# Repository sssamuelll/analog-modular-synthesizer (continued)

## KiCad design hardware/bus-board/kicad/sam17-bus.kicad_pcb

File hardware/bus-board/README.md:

# Bus board — distribución de ±12 V

Reparte los rieles del [módulo 1](../01-power-supply/) a los módulos. Sustituye
al daisy-chain con cables jumper de la tesis, que era la fuente de ruido y de
desafinación que la propia tesis reportó.

Se construyen **dos segmentos idénticos** de 320 × 60 mm. Cada uno lleva 6
slots y se alimenta con su propio par de cables desde el punto de estrella.

## Qué decide esta placa

No es un problema de corriente, es de **afinación**. A 1 V/octava, **1 mV de
diferencia de masa entre dos módulos son 1.2 cents** de error de tono. El
objetivo es ≤ 2 cents entre los cuatro módulos de la cadena de tono, y de ahí
sale todo lo demás.

| | |
|---|---|
| Presupuesto de masa medido | **1.21 cents** ([`ground_budget.py`](ground_budget.py)) |
| Masa | **plano sólido en B.Cu** — con pista de 5 mm serían +7.1 cents |
| Vías | **0** — una vía de señal le abre una ranura al plano |
| De dónde venimos | daisy-chain de la tesis: 6.3–30 cents |

El resultado que no esperaba: **el plano aporta solo 0.20 cents; el resto se lo
come el cable de bajada**. Y dentro del cable manda el contacto crimpado, no el
cobre. Detalle en [`notes/design-notes.md`](notes/design-notes.md).

## Por slot

- **Peine Eurorack 2×8 sin llave** — Doepfer prohíbe expresamente los headers
  con caja y código en un bus board. La franja roja va al par **−12 V**,
  serigrafiado. El +5 V, CV y Gate quedan **NC a propósito** (§9 de las notas).
- **Peine SAM17 KK-254 de 4 pines, con llave** — el mismo `J2` del módulo 1.
- **Dos PTC de 0.25 A**, uno por riel. **Nunca en masa**: ahí serían 94 cents.
- **Dos LED con 4k7** en paralelo con cada PTC. Apagados en marcha, encendidos
  cuando ese fusible dispara. Señalan el conector y el riel culpables.

## Estructura

```
bus-board/
├── ground_budget.py     El presupuesto de masa, ejecutable y con aserciones
├── bom.csv
├── kicad/
│   ├── symlib.py            Extrae simbolos de las librerias de KiCad
│   ├── build_schematic.py   Genera sam17-bus.kicad_sch (sin MCP: kicad-cli)
│   ├── check_netlist.py     Netlist contra el diseño declarado a mano
│   ├── check_bom.py         Cruce esquemático <-> bom.csv
│   ├── build_pcb.py         Genera sam17-bus.kicad_pcb (pcbnew directo)
│   └── sam17.pretty/        Huella propia del PTC (admite dos encapsulados)
├── schematics/ pcb/ fab/
└── notes/design-notes.md
```

## Estado

- [x] Presupuesto de masa cerrado y ejecutable — **1.21 cents** de 2
- [x] Esquemático — 49 componentes, **ERC 0 infracciones**
- [x] Netlist verificado contra el diseño: 27 redes, 160 pines, uno a uno
- [x] PCB — 320 × 60 mm, 2 capas, **DRC 0 infracciones, 0 sin conectar, 0 vías**
- [x] Masa en B.Cu verificada por id de capa (el nombre de capa engaña)
- [x] Gerbers y taladros en [`fab/`](fab/)
- [ ] **Antes de fabricar**: verificar con polímetro el orden de filas del peine
      Eurorack contra un cable Doepfer real. Está confirmado que la franja roja
      es −12 V; el orden del bloque central sale de fuentes secundarias
      ([§12.1](notes/design-notes.md))
- [ ] Medir la resistencia de contacto real del crimpado — es el término que más
      pesa del presupuesto y el valor usado es de manual
- [ ] Medir la diferencia de masa entre slots con los módulos montados

## Reglas de montaje que no se pueden saltar

1. **La cadena de tono (MIDI/CV + VCO1..3) va entera en el mismo segmento.**
   Repartida entre los dos, el desequilibrio entre sus cables de alimentación se
   les suma completo.
2. **Los dos hilos de masa del cable SAM17 se crimpan siempre.** Con uno solo el
   presupuesto se sale de los 2 cents.
3. **Cables de bajada ≤ 150 mm.** A 500 mm se añade ~1 cent.
4. **Separadores de nylon, no metálicos.** El puente chasis-masa es uno y está
   en el módulo 1 ([§13](../01-power-supply/notes/design-notes.md)).
5. **Cada segmento se alimenta desde el punto de estrella**, con pares de
   2.5 mm² de longitud parecida. No encadenar un segmento del otro.
6. **Franja roja del cable al par serigrafiado −12 V.** Siempre.

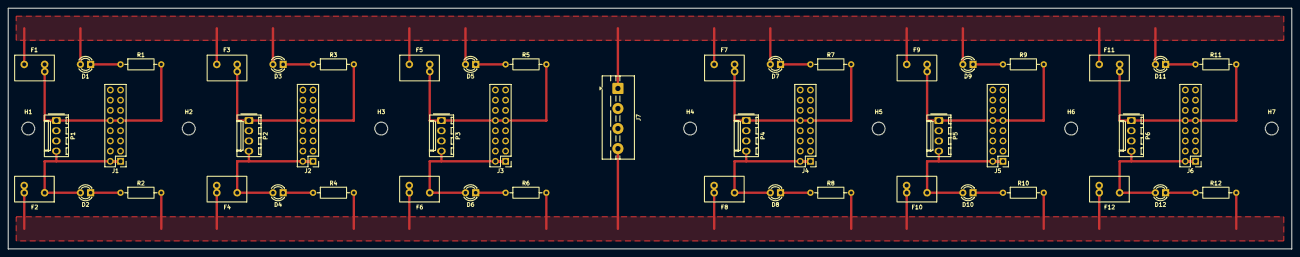
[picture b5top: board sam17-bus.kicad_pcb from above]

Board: 2 copper layers, 320.0 x 60.0 mm, 56 parts (0 on the bottom side), 27 nets.

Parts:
D1, D2, D3, D4, D5, D6, D7, D8, D9, D10, D11, D12: LED_D3.0mm
F1, F2, F3, F4, F5, F6, F7, F8, F9, F10, F11, F12: PTC_Radial_P5.08mm_Dual
H1, H2, H3, H4, H5, H6, H7: MountingHole_3.2mm_M3
J1, J2, J3, J4, J5, J6: PinHeader_2x08_P2.54mm_Vertical
J7: TerminalBlock_MaiXu_MX126-5.0-04P_1x04_P5.00mm
P1, P2, P3, P4, P5, P6: Molex_KK-254_AE-6410-04A_1x04_P2.54mm_Vertical
R1, R2, R3, R4, R5, R6, R7, R8, R9, R10, R11, R12: R_Axial_DIN0207_L6.3mm_D2.5mm_P10.16mm_Horizontal

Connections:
+12S1: F1.2, J1.9, J1.10, P1.1, R1.2
+12S2: F3.2, J2.9, J2.10, P2.1, R3.2
+12S3: F5.2, J3.9, J3.10, P3.1, R5.2
+12S4: F7.2, J4.9, J4.10, P4.1, R7.2
+12S5: F9.2, J5.9, J5.10, P5.1, R9.2
+12S6: F11.2, J6.9, J6.10, P6.1, R11.2
+12V: D1.2, D3.2, D5.2, D7.2, D9.2, D11.2, F1.1, F3.1, F5.1, F7.1, F9.1, F11.1, J7.1
-12S1: D2.2, F2.1, J1.1, J1.2, P1.4
-12S2: D4.2, F4.1, J2.1, J2.2, P2.4
-12S3: D6.2, F6.1, J3.1, J3.2, P3.4
-12S4: D8.2, F8.1, J4.1, J4.2, P4.4
-12S5: D10.2, F10.1, J5.1, J5.2, P5.4
-12S6: D12.2, F12.1, J6.1, J6.2, P6.4
-12V: F2.2, F4.2, F6.2, F8.2, F10.2, F12.2, J7.4, R2.2, R4.2, R6.2, R8.2, R10.2, R12.2
GND: J1.3, J1.4, J1.5, J1.6, J1.7, J1.8, J2.3, J2.4, J2.5, J2.6, J2.7, J2.8, J3.3, J3.4, J3.5, J3.6, J3.7, J3.8, J4.3, J4.4, J4.5, J4.6, J4.7, J4.8, J5.3, J5.4, J5.5, J5.6, J5.7, J5.8, J6.3, J6.4, J6.5, J6.6, J6.7, J6.8, J7.2, J7.3, P1.2, P1.3, P2.2, P2.3, P3.2, P3.3, P4.2, P4.3, P5.2, P5.3, P6.2, P6.3
unnamed: D1.1, R1.1
unnamed: D2.1, R2.1
unnamed: D3.1, R3.1
unnamed: D4.1, R4.1
unnamed: D5.1, R5.1
unnamed: D6.1, R6.1
unnamed: D7.1, R7.1
unnamed: D8.1, R8.1
unnamed: D9.1, R9.1
unnamed: D10.1, R10.1
unnamed: D11.1, R11.1
unnamed: D12.1, R12.1

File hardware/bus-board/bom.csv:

refs,value,footprint,quantity,supplier,notes
J1 J2 J3 J4 J5 J6,"Tira de pines 2x8 2.54 mm RECTA, SIN caja",Connector_PinHeader_2.54mm:PinHeader_2x08_P2.54mm_Vertical,6,Reichelt,"Peine Eurorack. SIN caja y SIN llave, y esto NO es un ahorro: Doepfer lo prohibe expresamente — 'it's not allowed to use bus boards with polarized pin headers (boxed pin headers with code gap). These force the user to connect the bus cable in a certain direction which may be the wrong one'. La orientacion la da la franja roja del cable = -12 V = par de abajo, serigrafiado en la placa. Si compras version con caja, la caja decide por ti y puede decidir mal"
P1 P2 P3 P4 P5 P6,"Molex KK-254 4 pines vertical (macho de PCB)",Connector_Molex:Molex_KK-254_AE-6410-04A_1x04_P2.54mm_Vertical,6,Mouser,"Peine SAM17. La MISMA pieza que J2 del modulo 1, para que el cable de bajada sea macho-hembra del mismo sistema. Aqui la llave SI se quiere: es un conector propietario, no hay estandar ajeno que respetar, y la llave impide invertirlo"
J7,"Bornero de tornillo 4 pos, paso 5 mm, >=2.5 mm2",TerminalBlock:TerminalBlock_MaiXu_MX126-5.0-04P_1x04_P5.00mm,1,Reichelt,"Entrada desde el punto de estrella del modulo 1: +12 / GND / GND / -12. Los DOS tornillos de masa se usan: dividen por dos la resistencia de contacto del feed. Que admita 2.5 mm2 no es capricho — con 1.5 mm2 el desequilibrio entre los dos segmentos se come 1 cent del presupuesto (ground_budget.py)"
F1 F2 F3 F4 F5 F6 F7 F8 F9 F10 F11 F12,"PTC reajustable 0.25 A hold / 0.50 A trip, >=30 V",sam17:PTC_Radial_P5.08mm_Dual,12,Mouser,"Bel Fuse 0ZRE0025FF1E (Ihold 0.25 A, Itrip 0.56 A, 240 V, R 1.3 ohm typ). Alternativa Bourns MF-R025 (Ihold 0.25 A, Itrip 0.50 A, 60 V, Rmin 1.00 / R1max 1.95 ohm) — la huella admite las DOS porque el pad 2 esta duplicado (patillas en linea o escalonadas). Se puebla UNO de los dos taladros. **Van en +12 V y en -12 V, JAMAS en masa**: 1.3 ohm en el retorno son 94 cents de desafinacion"
D1 D2 D3 D4 D5 D6 D7 D8 D9 D10 D11 D12,"LED 3 mm rojo difuso, alta eficiencia",LED_THT:LED_D3.0mm,12,Reichelt,"Indicador de PTC disparado, en paralelo con su fusible. Apagado en marcha (caen ~0.1 V sobre el PTC intacto) y encendido a ~2 mA cuando el PTC dispara y quedan los 12 V. Que sea de alta eficiencia importa: a 2 mA un LED antiguo no se ve. Dos por slot, uno por riel, porque el riel que falla es la mitad del diagnostico"
R1 R2 R3 R4 R5 R6 R7 R8 R9 R10 R11 R12,"4k7 1/4 W 5%",Resistor_THT:R_Axial_DIN0207_L6.3mm_D2.5mm_P10.16mm_Horizontal,12,Reichelt,"Limitadora del LED indicador. 4k7 da ~2.1 mA con 12 V sobre el PTC disparado. No bajar mucho: la rama roba corriente al PTC y este necesita seguir calentandose solo para quedarse disparado (a 12 V pide ~40 mA, asi que 2 mA no le molestan)"
H1 H2 H3 H4 H5 H6 H7,"Separador de NYLON M3 + tornillo de nylon",MountingHole:MountingHole_3.2mm_M3,7,Reichelt,"NYLON, no metal. Siete esparragos metalicos unirian el plano de masa al chasis en siete puntos y meterian corriente de chasis por el plano — justo lo que el presupuesto de masa da por supuesto que no pasa. El puente chasis-GND es UNO y esta en el modulo 1 (§13)"
—,"Cable de bajada SAM17: 4 hilos 24 AWG, <=150 mm",n/a,6,Reichelt,"Macho-hembra KK-254 de 4 vias. **Los dos hilos de masa se crimpan siempre**: con uno solo el presupuesto se dobla y se sale de los 2 cents. Y <=150 mm: a 500 mm se anaden ~1 cent. Engordar a 20 AWG casi no mejora — a esta escala mandan los contactos crimpados, no el cobre"
—,"Cable de bajada Eurorack: cinta 16 vias, <=150 mm",n/a,6,Thomann/Schneidersladen,"Cinta IDC estandar de 16 vias con franja roja. La franja va SIEMPRE al par de abajo, el serigrafiado -12V. Sus 6 conductores de masa en paralelo compensan que sea 28 AWG: sale a 9.1 mohm, mejor que los 16.8 del cable SAM17 de 24 AWG con solo dos"
—,"Alimentacion desde el modulo 1: 2.5 mm2, par por segmento",n/a,2,Reichelt,"Un par +12/GND/-12 por SEGMENTO, los dos saliendo del MISMO punto de estrella y lo mas iguales de largo que se pueda. Encadenar un segmento del otro seria mas comodo y mete la caida del primero en el segundo"

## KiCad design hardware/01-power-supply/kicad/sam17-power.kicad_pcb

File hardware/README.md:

# Hardware

Esquemáticos, PCBs y BOMs para los 7 módulos del SAM17.

| Módulo | Carpeta | Documentación |
|--------|---------|---------------|
| 1 — Alimentación | [`01-power-supply/`](01-power-supply) | [`docs/modules/01-power-supply.md`](../docs/modules/01-power-supply.md) |
| 2 — MIDI/CV | [`02-midi-cv/`](02-midi-cv) | [`docs/modules/02-midi-cv.md`](../docs/modules/02-midi-cv.md) |
| 3 — VCO | [`03-vco/`](03-vco) | [`docs/modules/03-vco.md`](../docs/modules/03-vco.md) |
| 4 — Mixer | [`04-mixer/`](04-mixer) | [`docs/modules/04-mixer.md`](../docs/modules/04-mixer.md) |
| 5 — VCF | [`05-vcf/`](05-vcf) | [`docs/modules/05-vcf.md`](../docs/modules/05-vcf.md) |
| 6 — ADSR | [`06-adsr/`](06-adsr) | [`docs/modules/06-adsr.md`](../docs/modules/06-adsr.md) |
| 7 — VCA | [`07-vca/`](07-vca) | [`docs/modules/07-vca.md`](../docs/modules/07-vca.md) |

Y una placa que no es un módulo de la tesis pero sin la cual los módulos no
afinan entre sí:

| Placa | Carpeta | Qué decide |
|---|---|---|
| Bus board | [`bus-board/`](bus-board) | Reparte ±12 V a todos. **1 mV de diferencia de masa entre dos módulos = 1.2 cents de desafinación**; el presupuesto está en [`bus-board/ground_budget.py`](bus-board/ground_budget.py) y sale a 1.21 de 2 |

## Estructura por módulo

Cada subdirectorio sigue la misma convención:

```
NN-<módulo>/
├── README.md            Resumen, especificaciones y mejoras
├── kicad/               Proyecto KiCad (.kicad_pro, .kicad_sch, .kicad_pcb)
├── schematics/          Esquemáticos exportados a PDF
├── pcb/                 Renderizados PCB (PNG/SVG/3D)
├── bom.csv              Lista de materiales
└── notes/               Notas de diseño, mediciones, calibración
```

## Convenciones eléctricas

Ver [`docs/architecture.md`](../docs/architecture.md) para el detalle del bus
de alimentación, niveles de señal y estándar 1 V/octava compartido por
todos los módulos.

## Estado actual

Este es el esqueleto inicial: los proyectos KiCad, esquemáticos y PCBs
todavía no están versionados. Las BOM contienen una **versión preliminar**
extraída de la tesis (Tabla 8 y 9 de la evaluación económica). Si vas a
empezar a capturar el esquemático de un módulo, abre primero un *issue*
para evitar trabajo duplicado.

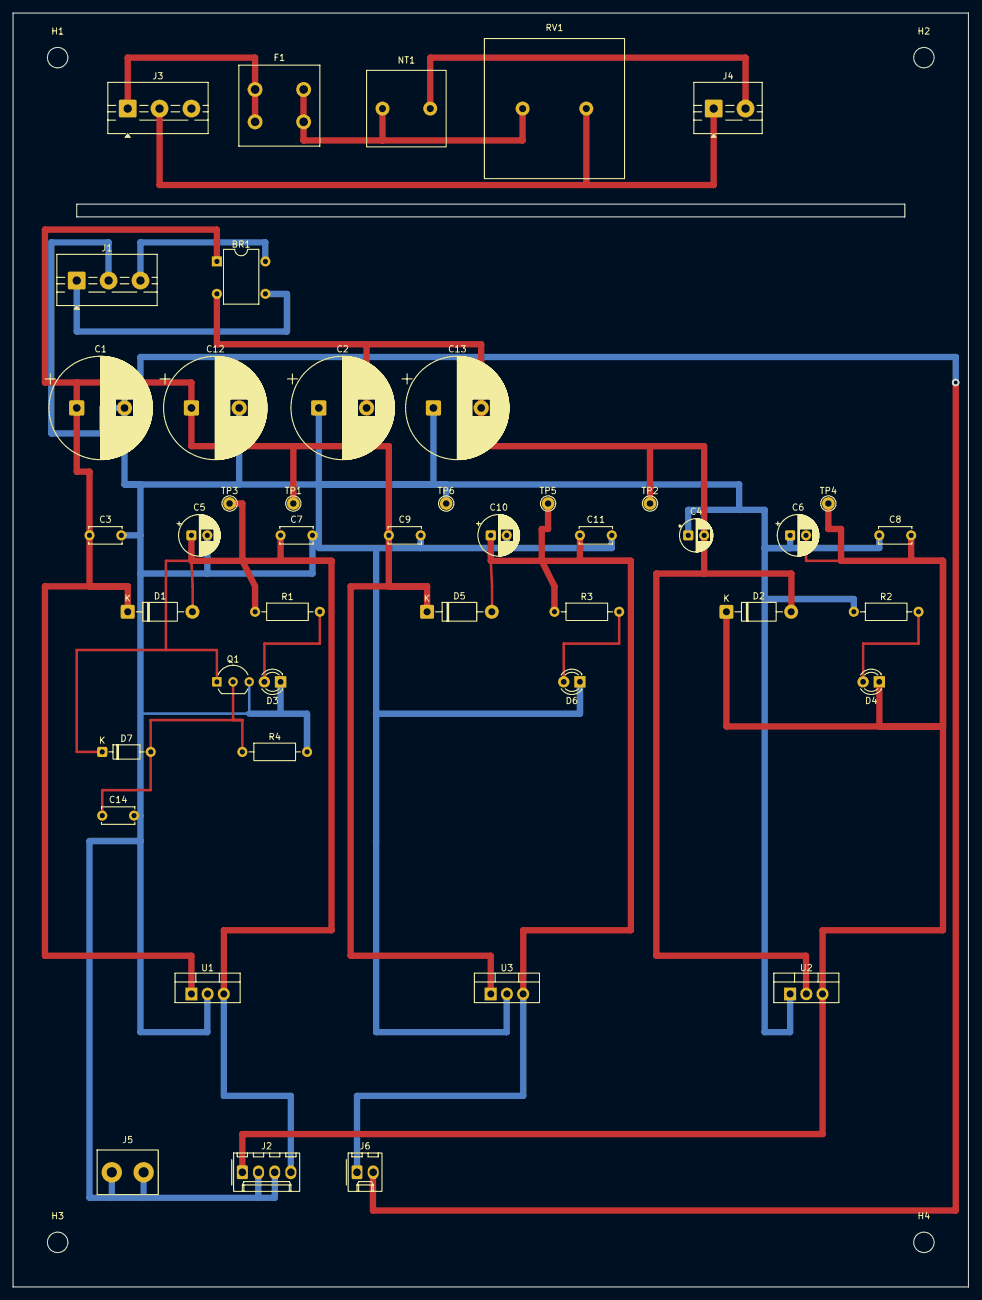
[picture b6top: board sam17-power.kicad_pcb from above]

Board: 2 copper layers, 150.0 x 200.0 mm, 49 parts (0 on the bottom side), 16 nets.

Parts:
BR1: Diode_Bridge_DIP-4_W7.62mm_P5.08mm
C1, C2, C12, C13: CP_Radial_D16.0mm_P7.50mm
C3, C7, C8, C9, C11, C14: C_Disc_D5.0mm_W2.5mm_P5.00mm
C4: CP_Radial_D5.0mm_P2.50mm
C5, C6, C10: CP_Radial_D6.3mm_P2.50mm
D1, D2, D5: D_DO-41_SOD81_P10.16mm_Horizontal
D3, D4, D6: LED_D3.0mm
D7: D_DO-35_SOD27_P7.62mm_Horizontal
F1: Fuseholder_Cylinder-5x20mm_Schurter_FPG4_Vertical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; Fuseholder_Cylinder-5x20mm_Schurter_FPG4_Vertical_Closed
H1, H2, H3, H4: MountingHole_3.2mm_M3
J1, J3: TerminalBlock_MaiXu_MX126-5.0-03P_1x03_P5.00mm
J2: Molex_KK-254_AE-6410-04A_1x04_P2.54mm_Vertical
J4: TerminalBlock_MaiXu_MX126-5.0-02P_1x02_P5.00mm
J5: Faston_6.3x0.8mm_PCB_2Leg_P5.0mm
J6: Molex_KK-254_AE-6410-02A_1x02_P2.54mm_Vertical
NT1: NTC_Disc_D11.5mm_W4.5mm_P7.5mm
Q1: TO-92_Inline_Wide
R1, R2, R3, R4: R_Axial_DIN0207_L6.3mm_D2.5mm_P10.16mm_Horizontal
RV1: RV_Disc_D21mm_W5.5mm_P10.0mm
TP1, TP2, TP3, TP4, TP5, TP6: TestPoint_THTPad_D2.0mm_Drill1.0mm
U1, U2, U3: TO-220-3_Vertical

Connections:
+5V: C10.1, C11.1, D5.2, J6.1, R3.1, TP5.1, U3.3
+12V: C5.1, C7.1, D1.2, D7.1, J2.4, Q1.1, R1.1, TP3.1, U1.3
-12V: C6.2, C8.2, D2.1, D4.1, J2.1, TP4.1, U2.3
/L: F1.1, J3.1
/L_F: F1.2, NT1.1, RV1.1
/L_TR: J4.2, NT1.2
/N: J3.2, J4.1, RV1.2
/SEC_A: BR1.3, J1.1
/SEC_B: BR1.4, J1.3
/VRAW+: BR1.1, C1.1, C3.1, C9.1, C12.1, D1.1, D5.1, TP1.1, U1.1, U3.1
/VRAW-: BR1.2, C2.2, C4.2, C13.2, D2.2, TP2.1, U2.2
GND: C1.2, C2.1, C3.2, C4.1, C5.2, C6.1, C7.2, C8.1, C9.2, C10.2, C11.2, C12.2, C13.1, C14.2, D3.1, D6.1, J1.2, J2.2, J2.3, J5.1, J6.2, Q1.3, R2.1, R4.2, TP6.1, U1.2, U2.1, U3.2
unnamed: D3.2, R1.2
unnamed: D4.2, R2.2
unnamed: D6.2, R3.2
unnamed: C14.1, D7.2, Q1.2, R4.1

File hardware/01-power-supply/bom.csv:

refs,value,footprint,quantity,supplier,notes,
TR1,230VAC pri / 12-0-12 VAC 2A (24V totales con toma central),external,1,Reichelt/Mouser,Transformador externo — variante EU (230VAC/50Hz); ver design-notes.md §12 y §15. ATENCIÓN: son 12-0-12 (24 V totales),"[' NO 12 V totales. Muchos vendedores llaman «12V CT» a un 6-0-6: con ese cada riel daría ~7.6 V y el 7812 no regularía nunca. Pedir además la tensión de secundario EN VACÍO: hace falta ≥13.3 V por semidevanado (regulación ≥10.7%) para que el riel de +12 V aguante la red al -10% a plena carga de diseño — simulado', ' ver simulations/power. No va en la placa: entra por J4 (primario) y vuelve por J1 (secundario)']"
F1,Fuse 250mA slow + portafusible CERRADO 5x20,Fuseholder_Cylinder-5x20mm_Vertical_Closed,1,Reichelt/Mouser,Protección primario 230VAC — variante EU (§12). Cerrado,"[' no de clips abiertos: son 230 V dentro de un cajón de madera y el aislamiento elegido es reforzado (§14). Referencia tipo Schurter FPG4 (IEC 60335-1', ' 250VAC/10A VDE)']"
RV1,S20K275 / V275LA20A,sam17:RV_Disc_D21mm_W5.5mm_P10.0mm,1,Reichelt/Mouser,Supresor de transitorios en primario (20mm 275VAC para red 230VAC) — variante EU (§12). Va DESPUÉS de F1 para que un MOV en corto funda el fusible,
NT1,SL10-5R020 (5Ω 2A),sam17:NTC_Disc_D11.5mm_W4.5mm_P7.5mm,1,Reichelt/Mouser,Inrush limiter en serie con el primario AC (rated 265VAC — sirve igual en EU sin cambios),
BR1,KBP206 (2A / 600V) o equivalente DIP-4,Diode_Bridge_DIP-4_W7.62mm_P5.08mm,1,Reichelt,Puente rectificador. ATENCIÓN antes de fabricar: verificar el ORDEN DE PATILLAS contra el datasheet de la pieza comprada. El símbolo del esquemático es D_Bridge_+-AA (pin1=+,"[' pin2=−', ' pin3=~', ' pin4=~) y KiCad trae cinco variantes porque el orden cambia según el fabricante (§14)']"
U1,LM7812,TO-220,1,Reichelt,Regulador +12V (con zócalo),
U2,LM7912,TO-220,1,Reichelt,Regulador -12V (tab = -Vin — aislar del chasis),
U3,LM7805,TO-220,1,Reichelt,Regulador +5V para LCD y AD5686R,
"C1,C2",4700uF/25V electrolytic (ripple ≥1.2A @100Hz),CP_Radial_D16.0mm_P7.50mm,2,Reichelt,Corriente de rizado simulada: 0.72-0.88 A RMS (§15). Bulk tras el puente — uno por riel (+V y -V). Diámetro 16 mm y paso 7.5 mm: el footprint que pedía este BOM (D10) no existe para 4700 µF/25 V — un D10 a esa tensión ronda los 470 µF,
"C3,C4,C9",0.33uF ceramic,C_Disc_D5_W2.5_P5,3,Reichelt,Entrada de cada regulador (TI app note),
"C5,C6,C10",100uF/25V electrolytic,Radial-D6.3,3,Reichelt,Salida de cada regulador,
"C7,C8,C11",0.1uF ceramic,C_Disc_D5_W2.5_P5,3,Reichelt,Bypass HF en salida de regulador,
"D1,D2,D5",1N4001,DO-41,3,Reichelt,Diodos de protección anti-backfeed (uno por riel),
D3,LED rojo 3mm,LED-3mm,1,Reichelt,Indicador +12V,
D4,LED amarillo 3mm,LED-3mm,1,Reichelt,Indicador -12V,
D6,LED verde 3mm,LED-3mm,1,Reichelt,Indicador +5V,
"R1,R2",2.2k 1/4W,R_Axial,2,Reichelt,Limitadora de los LED de ±12V (~4.5 mA),
R3,680R 1/4W,R_Axial,1,Reichelt,Limitadora del LED de +5V. NO son 2.2k: a 5V darían ~1.3 mA y el LED queda apagado; 680R deja los mismos ~4.5 mA que los otros dos rieles,
"HS1,HS2,HS3",Heatsink TO-220 Rth<=20 C/W,—,3,Reichelt,Disipadores con aleta (uno por regulador) — mecánico,[' no aparece en el esquemático']
"XU1,XU2,XU3",TO-220 socket,—,3,Reichelt,Zócalo para reguladores (hot-swap si falla) — mecánico,[' no aparece en el esquemático']
J1,Barrier block 3 pos,TB-3,1,Reichelt,Entrada del secundario del transformador. Son TRES posiciones y no dos: el secundario es de toma central (12VAC CT) y lleva tres hilos — 12VAC / CT / 12VAC,
J2,Molex KK-254 4 pos (o pin header 1x4 con llave),KK-254-4,1,Reichelt,Bus analógico +12/GND/GND/-12 hacia los módulos 2-7. Resuelto en issue #8 (opción C): el +5V NO va por aquí — sale por J6 con retorno dedicado (§10.1/§10.4). Con llave/polarizado para que no se pueda enchufar al revés,
J3,Barrier block 3 pos,TB-3,1,Reichelt,Entrada AC primaria: L / N / PE. El pin 3 (PE) no lleva pista en la PCB — sale por cable al espárrago del chasis (§13),
J4,Barrier block 2 pos,TB-2,1,Reichelt,Salida hacia el primario de TR1 (después de F1 + RV1 + NT1). Dibujado girado: J4.2 = línea y J4.1 = neutro — en un primario da igual cuál es cuál porque el devanado es flotante,
J5,Faston macho 6.3mm PCB (2 patillas),sam17:Faston_6.3x0.8mm_PCB_2Leg_P5.0mm,1,Reichelt,Puente único GND ↔ chasis (§13). Va al MISMO espárrago que el PE de J3 y a ningún otro sitio,
J6,Molex KK-254 2 pos (distinto de J2),KK-254-2,1,Reichelt,Feed de +5V al módulo 2 (AD5686R + LCD ~150 mA). Conector aparte del bus a propósito (issue #8 opción C): retorno dedicado hasta el punto de estrella (§10.1) y de 2 posiciones — imposible cruzarlo con el bus de ±12,
—,Espárrago M4 + tuerca + contratuerca + arandela dentada,—,1,Reichelt,Punto único de tierra del equipo (§13). Solo lo usan el PE del cable de red y el puente de J5. Ningún otro tornillo comparte ese espárrago,
—,Terminal de anillo M4 para 1.0 mm²,—,2,Reichelt,Uno para el PE del cable de red y otro para el puente de J5 (§13),
—,Cable 1.0 mm² verde/amarillo,—,1,Reichelt,Puente J5 → espárrago. El verde/amarillo está reservado por norma a tierra de protección: no usarlo para nada más (§13),
—,Prensaestopas / pasacables con retención de tracción,—,1,Reichelt,Entrada del cable de red al cajón. El conductor PE se corta más largo que L y N para que sea el último en soltarse si se tira del cable (§13),
